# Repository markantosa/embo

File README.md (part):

# EMBO — Embolization Particle Sizing System

> SUTD 30.007 Engineering Design Innovation | Team EMBO | Week 13 of 13

EMBO is a closed-loop medical device that automates and quality-controls the preparation of gelatin foam embolic agents for interventional radiology procedures. It is the first device of its kind to measure and control particle size during embolic agent preparation in real time.

| | |
|:---:|:---:|
|  |  |
| *Fully assembled device* | *Electrical assembly* |

**CAD renders**

| Isometric | Front | Sheet-metal enclosure |
|:---:|:---:|:---:|
|  |  |  |
| *First concept render (Blender)* | *First concept render (Blender)* | *CAD (Fusion 360)* |

---

## The Problem

Embolization procedures use tiny gelatin foam particles (embolic agents) to deliberately block blood vessels — treating tumours, fibroids, and bleeding. Before every procedure, a clinician manually prepares a particle slurry by pumping two syringes back and forth until the mixture reaches a "pudding consistency." There is no measurement, no standard, and no quality check. Two clinicians doing this side by side produce slurries with completely different particle size distributions. Particle size directly affects clinical outcomes: wrong sizes can cause tissue death in unintended areas or fail to block the target vessel.

**No device currently exists to measure or control particle size during this preparation step.** Gelfoam has been used since the 1970s with the preparation method unchanged.

---

## What EMBO Does

EMBO replaces manual syringe pumping with a controlled, sensor-guided system that:

1. **Automates mixing** — two stepper motors drive syringe plungers back and forth with precise speed, stroke, and cycle control
2. **Measures particle size** using two independent sensing modalities:
   - **Ultrasound attenuation (UAS)** — a 1 MHz acoustic signal chain measures how much sound energy the slurry absorbs; larger particles attenuate more. This is the **closed-loop** measurement the mixing stop condition actually runs on.
   - **Computer vision (verification only)** — a Raspberry Pi Zero 2W + OV9281 global-shutter mono camera captures a frame on demand and runs it through a Roboflow-hosted instance-segmentation model, reporting median particle size and IQR plus a segmentation-blob-annotated photo. This is an **optional, operator-triggered check**, not a continuous control input — see "Sensing System" below for why.
3. **Stops automatically** when the target particle size is reached, using a closed-loop control scheduler on the ESP32-S3 driven by the UAS delta-voltage size equation, adjusting stroke-by-stroke based on live sensor feedback. The target is adjustable per procedure (50–1000 µm, set via the touchscreen/encoder), since the ideal size depends on which vessels are being treated.

---

## System Architecture

```
┌─────────────────────────────────────────────────────────────────┐
│                        EMBO Device                              │
│                                                                 │
│  ┌──────────────────┐          ┌──────────────────────────────┐ │
│  │ Raspberry Pi     │◄─UART──►│     ESP32-S3 MCU Board       │ │
│  │ Zero 2W          │          │                              │ │
│  │  - Roboflow      │          │  - Scheduler control loop    │ │
│  │    hosted CV     │          │    (UAS delta-V closed loop) │ │
│  │    (on-demand)   │          │  - 2× TMC2209 motor drivers  │ │
│  │  - Particle size │          │  - UAS signal chain          │ │
│  │    + annotated   │          │  - ILI9341 TFT UI (LovyanGFX)│ │
│  │    photo         │          │  - BLE debug (NimBLE)        │ │
│  │  - OV9281 CSI    │          │                              │ │
│  │    mono camera   │          │                              │ │
│  └──────────────────┘          └──────────────────────────────┘ │
│           │                             │           │            │
│           ▼                             ▼           ▼            │
│    [Camera + LED]              [Stepper motors] [UAS Transducers]│
│    [Backlight panel]           [Limit switches] [SMA connectors] │
└─────────────────────────────────────────────────────────────────┘
```

### Particle Size Model

Mixing follows first-order breakage kinetics:

```
D(N) = D_min + (D₀ − D_min) × e^(−kN)
```

Where `N` is stroke count, `k` is a shear constant (measured empirically), `D₀` is initial particle size, and `D_min` is the minimum achievable size. The mixing scheduler uses live measurements of `D(N)` (via the UAS delta-V equation) to decide when to stop.

---

## Repository Structure

```
EMBO/
├── README.md
├── .gitignore
│
├── docs/                              # Design documents and briefs
│   ├── EMBO_Project_Overview.md       # Project context — public/general audience
│   ├── EMBO_PCB_Design_Brief_v3_4.txt # Complete electrical design spec (current)
│   ├── EMBO_PCB_Design_Brief_v3_4.docx / .pdf
│   ├── EMBO_PCB_Design_Brief_v2.51.txt# Superseded — kept for reference
│   └── EMBO_Pinout_Cheatsheet.txt     # Quick GPIO and connector reference (being updated for v3.4)
│
├── hardware/
│   ├── electrical/                    # KiCad schematics + PCB layout — 2 boards:
│   │   │                              #   main board (v3.4, current) + display breakout
│   │   └── README.md
│   └── mechanical/                    # CAD files (SolidWorks / Fusion 360)
│                                      #   Final Pure Assembly.f3z is the current top-level assembly
│       └── README.md
│
├── firmware/
│   └── esp32/                         # ESP32-S3 Arduino/C++ firmware (PlatformIO)
│       ├── README.md                  # Flash guide and peripheral notes
│       └── ../FIRMWARE_TODO.md        # Build-up task list + hardware checklist
│
├── software/
│   ├── SOFTWARE_TODO.md               # Original CV pipeline build-up task list (superseded, kept for reference)
│   ├── cv_verify/                     # CURRENT — on-demand CV verification, Pi Zero 2W
│   │   ├── SESSION_HANDOFF.md         # Latest working state, Roboflow wiring, hardware notes
│   │   ├── main.py                    # Request/reply loop: waits for CAPTURE, replies SIZE + annotated IMG
│   │   ├── capture.py / preprocessing.py / link.py / config.py
│   │   └── SETUP.md                   # Pi Zero 2W flash/SSH/dev setup
│   └── cv-pipeline/                   # Legacy — original continuous-loop design, Pi 5 + YOLOv8.
│       │                              # detection.py/sizing.py now live here and are imported by
│       │                              # cv_verify/main.py (loop-agnostic), but the driving loop itself
│       │                              # moved to cv_verify/ — see cv_verify/TODO.md for why.
│       └── README.md
│
├── testing/
│   ├── PCB_Test_Firmware_v3_4/        # v3.4 bench-test firmware + Web Bluetooth sensor dashboard
│   └── CV_Verify_UART_Prototype/      # Throwaway prototype that proved out the IMG-over-UART
│                                      # protocol ahead of real detection/sizing existing — since
│                                      # merged into firmware/esp32/ directly, kept for reference
│
└── assets/                            # Images, diagrams, photos
```

Note: TFT touchscreen UI code lives in `firmware/esp32/src/ui.cpp` and is tracked in `firmware/FIRMWARE_TODO.md` — there's no separate `software/ui/` folder, since that code only runs on the ESP32, not the Pi.

---

## Hardware Overview

### Main MCU Board (ESP32-S3) — v3.4

| Subsystem | Components |
|---|---|
| Microcontroller | ESP32-S3-WROOM-1-N4 (4MB flash, no PSRAM, BLE 5.0, USB-C native programming) — corrected from N8 in v3.3, no pinout impact |
| Motor drivers | 2× MKS TMC2209 V2.0 plug-in modules in 2×8 sockets, field-replaceable; MS1/MS2 jumpers (new v3.4) make both modules interchangeable across UART addresses |
| Ultrasound signal chain | AD9833 DDS → OPA2354 Tx (G=4.9, 2.96Vpp) → transducer → OPA2354 Rx (G=100, interstage AC-coupled) → BAT54 envelope → GPIO1 ADC |
| Turbidity sensing | APDS9960 (I2C 0x39, ALS transmission) + MAX30102 (I2C 0x57, backscatter), shared I2C bus |
| Force sensing | 2× load cell + HX711 amplifier, socketed, shared-clock bit-bang driver — hardware fallback for StallGuard SG_RESULT |
| Display | ILI9341 SPI TFT + XPT2046 resistive touch via 20-pin IDC ribbon to breakout board |
| Power | 24V PSU → F1 (off-board T5A fuse) → F2 (on-board 8A backstop, new v3.4) → AO4407A reverse polarity protection → LM2596 buck (5V) → AMS1117 LDO (3.3V) |
| Comms | UART2 to Raspberry Pi (921600 baud, GPIO47/48); BLE UART debug stream (NimBLE) |

v3.4 is a hardware-hardening pass: 12× 220Ω GPIO protection resistors on every ESP32-to-TMC2209 control line (added after a hot-swap/spark incident on the fabricated v2.51 board), the PDN_UART pin correction (module pin 5, not pin 4), and a full reference-designator naming pass. See [`hardware/electrical/README.md`](hardware/electrical/README.md) for the complete changelog.

| | | |
|:---:|:---:|:---:|
|  |  |  |
| *3D render, front* | *3D render, back* | *KiCad trace routing — L1 + L4 (L2 GND, L3 3V3 hidden for clarity)* |

| | |
|:---:|:---:|
|  |  |
| *Fabricated board — bring-up* | *Fabricated board — wired up* |

### GPIO Assignments (key signals)

| GPIO | Signal | Notes |
|---|---|---|
| 1 | UAS_ADC | ADC1_CH0 — envelope detector output |
| 3/43 | I2C_SDA/SCL | Shared bus, APDS9960 (0x39) + MAX30102 (0x57), 400kHz |
| 4/44 | TMC_UART TX/RX | Half-duplex, shared PDN bus, via 1kΩ + 220Ω GPIO protection per module |
| 5/8 | STEP_M1/M2 | Hardware timer — step pulse generation, 220Ω GPIO protection |
| 6/9 | DIR_M1/M2 | Motor direction, 220Ω GPIO protection |
| 7/10 | EN_M1/M2 | Motor enable (active LOW, 10kΩ pull-up at IC), 220Ω GPIO protection |
| 14/15 | LIMIT_M1/M2 | Limit switch inputs (internal pull-up) |
| 19/20 | USB D−/D+ | Fixed USB PHY — no UART bridge chip needed |
| 21/37/42 | HX711_2_DT / SCK (shared) / HX711_1_DT | 2× load cell amplifiers, shared clock |
| 35/36 | SPI MOSI/CLK | Shared: AD9833 (Mode 2) + ILI9341 + XPT2046 (Mode 0) |
| 47/48 | RPi TX/RX | UART2 to Raspberry Pi, 921600 baud |

### Display Breakout Board — 2-layer PCB

ILI9341 TFT + XPT2046 touch controller on a separate board, connected to the main MCU board via a 20-pin IDC ribbon.

| | |
|:---:|:---:|
|  |  |
| *PCB layout* | *3D render* |

### Sensing System

**Ultrasound Attenuation Sensing (UAS):**
- AD9833 generates 1 MHz sine wave → OPA2354 Tx amp (G=4.9, 2.96Vpp output) → J1 SMA → transducer
- Received signal → J2 SMA → BAV99 protection → OPA2354 two-stage Rx (10× + 10× = 100× total) → BAT54 envelope detector → GPIO1
- Firmware reads attenuation ratio vs saline baseline to track particle size change

**Computer Vision (verification, not closed-loop control):**
- Raspberry Pi Zero 2W + OV9281-110 global-shutter mono CSI camera — no dye/contrast agent added to the slurry (real medical-device material), so contrast comes entirely from dark-field/oblique illumination and software-side local-contrast enhancement
- Operator-triggered only: the ESP32 sends `CAPTURE` over UART, the Pi captures + median-stacks frames (noise reduction), runs instance segmentation via a Roboflow-hosted model (RF-DETR, trained on ~100 collected samples), and replies with `SIZE <median_um> <iqr_um>` plus a downscaled photo with segmentation blob outlines baked in — both rendered on the touchscreen's Camera Verify screen side by side, with an IN SPEC/OUT OF SPEC check
- **Not a fusion input** — unlike UAS, a CV result never drives the mixing stop condition; worst case for a failed/slow capture is a timeout notice, not a stalled run. See `software/cv_verify/TODO.md` for the full reasoning
- Diffused LED panel (5V, J8) backlit behind syringe for particle contrast

**Turbidity Sensing (added v3.2, hardened v3.4):**
- APDS9960 (I2C 0x39) reads ALS clear-channel transmission through the syringe; external LED hardwired on
- MAX30102 (I2C 0x57) reads backscatter using its own onboard 660/880nm LEDs
- Shared I2C bus (GPIO3/GPIO43, 400kHz); independent of the UAS acoustic path — a second, optical estimate of slurry turbidity
- Live readings viewable on the BLE **Telemetry Dashboard** (`firmware/esp32/web/`) as Optical Sensor 1/2, alongside every other sensor — see "Getting Started" below
- Like CV, not yet part of the mixing stop condition — the fusion calibration table (`calibration.cpp`) is still unfilled placeholder data for every channel, so only UAS drives the closed loop today

**Force Sensing (added v3.2):**
- 2× load cell + HX711 24-bit amplifier at the syringe plunger contact point
- Shared-clock, per-channel data line — custom bit-bang driver (standard HX711 libraries assume one dedicated clock per chip)
- Hardware fallback for TMC2209 StallGuard SG_RESULT if the UART-based reading proves unreliable

---

## Firmware Status

| Module | File | Status |
|---|---|---|
| TMC2209 UART, SpreadCycle, StallGuard | `src/motors.cpp` | ✅ Done |
| LEDC step generation, limit switch ISRs | `src/motors.cpp` | ✅ Done |
| Homing routine + stroke counter | `src/motors.cpp` | ✅ Done |
| AD9833 1MHz DDS, UAS ADC calibration | `src/uas.cpp` | ✅ Done |
| NimBLE wireless debug UART + binary telemetry service | `src/ble_debug.cpp`, `src/ble_binary_telemetry.cpp` | ✅ Done |
| RPi UART: SIZE reply parsing + on-demand IMG (annotated photo) receive | `src/rpi_uart.cpp` | ✅ Done |
| Mixing scheduler: adjustable setpoint (50–1000µm), closed-loop UAS delta-V stop condition | `src/scheduler.cpp` | ✅ Done — replaces the old PID design |
| TFT UI: encoder-driven menus, live verify screen (photo + PSD/IQR), start/stop-estop | `src/ui.cpp`, `src/ui/screens/` | ⚠️ Touch input still stub (encoder-only works) |
| Turbidity sensors (APDS9960 + MAX30102) | `src/turbidity.cpp` | ✅ Done — feeds the BLE Telemetry Dashboard; not yet a fusion input (calibration table unfilled) |

See [`firmware/FIRMWARE_TODO.md`](firmware/FIRMWARE_TODO.md) for the full task list and hardware bring-up checklist, and [`firmware/esp32/README.md`](firmware/esp32/README.md#operational-workflow) for the doctor-facing operational workflow (boot → home → set target → run → stop/e-stop).

---

## Software Stack

| Layer | Platform | Language | Key Libraries |
|---|---|---|---|
| Computer vision (on-demand verification) | Raspberry Pi Zero 2W | Python 3 | picamera2, Pillow, NumPy, `requests` (Roboflow hosted inference — see `software/cv_verify/detection.py`) |
| Firmware / mixing scheduler | ESP32-S3 | C++ (Arduino) | TMCStepper, NimBLE, LovyanGFX, AD9833 |
| Touchscreen UI | ESP32-S3 | C++ | LovyanGFX |
| BLE debug + telemetry | ESP32-S3 | C++ | NimBLE |

**Critical firmware notes:**
- SPI2 is shared between AD9833 (Mode 2, ~10MHz), ILI9341 (Mode 0, 20MHz max via ribbon), and XPT2046 (Mode 0, 2MHz). Each library switches mode per transaction via `SPI.beginTransaction()`.
- TMC2209 uses a half-duplex UART bus (GPIO4 TX / GPIO44 RX as of v3.4). Raspberry Pi uses UART2 (GPIO47/48). These are separate peripherals — do not reassign.
- ADC1 (GPIO1) is safe while BLE is active. ADC2 cannot be used for analog during BLE — no ADC2 pins are used for analog in this design.
- SpreadCycle must be written via UART to both TMC2209 modules at every boot (no SPREAD pin on the MKS V2.0 modules). BLE log confirms success.
- HX711 reads are pinned to core 1 and short-critical-sectioned — PD_SCK must never sit HIGH past ~60µs or the chip powers itself down mid-read.

---

## Team Structure

| Sub-team | Responsibilities | Members |
|---|---|---|
| **Mechanical** | Frame, syringe holders, motor mounts, 3D printed enclosure (FDM + SLA resin), DOE (Design of Experiments) | Alvin, Victoria, Tian Wen |
| **Electrical & Software** | KiCad schematics + PCB layout (main board + display breakout), component sourcing, board bring-up/testing, ESP32-S3 firmware (mixing scheduler, motor control, UAS), RPi CV verification pipeline (Roboflow), TFT UI | Vincent, Ren Jie, Audrey, Aditi |

---

## Project Timeline

| Milestone | Week | Status |
|---|---|---|
| System Requirements Review | 5 | ✅ Complete |
| Recess week — build sprint | 7 | ✅ Complete |
| PCB schematic freeze | End of 7 | ✅ Complete |
| System Design Review | 9 | ✅ Complete |
| Final Exhibition | 13 | ✅ Current |

---

## Getting Started

### Firmware (ESP32-S3)

Requires VS Code + PlatformIO extension. See [`firmware/esp32/README.md`](firmware/esp32/README.md) for the full flash guide.

```bash
# Quick start
cd firmware/esp32
pio run --target upload   # build and flash
pio device monitor        # serial monitor at 115200
```

Hold `BOOT` + press `RESET` for manual bootloader entry if auto-reset fails.

### Computer Vision Pipeline (Raspberry Pi Zero 2W)

```bash
cd software/cv_verify
python3 -m venv .venv --system-site-packages   # --system-site-packages: sees apt-installed picamera2
source .venv/bin/activate
pip install -r ../requirements.txt
export ROBOFLOW_API_KEY=<your key>             # not stored in any committed file
python3 main.py
```

See [`software/cv_verify/SETUP.md`](software/cv_verify/SETUP.md) for full Pi Zero 2W bring-up (camera/UART dtoverlays, etc.) and [`software/cv_verify/SESSION_HANDOFF.md`](software/cv_verify/SESSION_HANDOFF.md) for current working state and known issues.

### Electrical

PCB files live in `hardware/electrical/` — two boards: the main board (`embo main MCU PCB v3_4/`, current revision) and the display breakout. Open with KiCad 10. The full design spec including component values, GPIO assignments, layout rules, BOM, and the pre-submission checklist is in [`docs/EMBO_PCB_Design_Brief_v3_4.txt`](docs/EMBO_PCB_Design_Brief_v3_4.txt).

### Telemetry Dashboard (real firmware)

`firmware/esp32/web/index_logging to record UAS csv data.html` is a Web Bluetooth dashboard for the actual production firmware (not the bench-test project below) — live UAS envelope, both load cells, and both optical/turbidity sensors (labeled Optical Sensor 1/2), plus motor jog/home controls and the automated UAS frequency sweep. Requires BLE to be enabled on-device first (**Settings → Developer mode → UAS debug mode**), and must be served over http(s) — Web Bluetooth silently fails under a `file://` URL:

```bash
cd firmware/esp32/web
python3 -m http.server 8000
# open http://localhost:8000/index_logging%20to%20record%20UAS%20csv%20data.html
```

### PCB Bench-Test Firmware + Dashboard

`testing/PCB_Test_Firmware_v3_4/` is a separate, standalone PlatformIO project for bringing up an assembled v3.4 board pre-final-firmware: reads every sensor (UAS envelope, both load cells, both turbidity channels, both StallGuard results, limit switches), drives the two steppers, and streams it all over BLE to its own Web Bluetooth dashboard (`web/index.html`) with live strip-charts alongside the raw numbers.

---

## Key References

- Yamagami et al., *The Size of Gelatin Sponge Particles*, CardioVascular and Interventional Radiology, 2006
- Yamamoto et al., CVIR 1997 — liver necrosis vs particle size
- PMC8670118 — hemorrhoidal embolization outcomes
- TMC2209 Datasheet — StallGuard4, SpreadCycle, UART addressing
- AD9833 Datasheet — DDS signal generator, SPI Mode 2
- OPA2354 Datasheet — 250MHz GBW dual op-amp, single-supply operation
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
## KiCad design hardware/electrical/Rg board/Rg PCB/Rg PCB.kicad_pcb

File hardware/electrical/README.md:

# Electrical — Custom MCU Board

KiCad schematic and PCB layout for the EMBO ESP32-S3 control board.

Current fabricated/in-progress revision: **v3.4** (`hardware/electrical/embo main MCU PCB v3_4/`).
The prior `embo main MCU PCB v2_5/` folder is kept for reference only — see
below for what changed between them.

## Design spec

Full design specification, component values, GPIO assignments, layout rules, BOM, and pre-submission checklist:
[`/docs/EMBO_PCB_Design_Brief_v3_4.txt`](../../docs/EMBO_PCB_Design_Brief_v3_4.txt)

Quick GPIO and connector reference:
[`/docs/EMBO_Pinout_Cheatsheet.txt`](../../docs/EMBO_Pinout_Cheatsheet.txt)
(being updated for v3.4 — treat the design brief above as authoritative in the meantime)

## Quick reference

- **MCU:** ESP32-S3-WROOM-1-N4 (4MB flash, no PSRAM, PCB antenna) — corrected from N8 in v3.3; no pinout impact, flash capacity only affects OTA partitioning
- **Motor drivers:** 2× MKS TMC2209 V2.0 plug-in modules in 2×8 sockets — field-replaceable, MS1/MS2 jumpers make both modules interchangeable across UART addresses 0–3 (new v3.4)
- **Turbidity sensing:** APDS9960 (I2C 0x39, ALS transmission) + MAX30102 (I2C 0x57, backscatter), shared I2C bus
- **Force sensing:** 2× load cell + HX711 amplifier, socketed, shared-clock — hardware fallback for StallGuard SG_RESULT
- **Signal generator:** AD9833 plug-in breakout module (VCC/DGND/SDATA/SCLK/FSYNC/AGND/OUT)
- **Fuse:** 5×20mm slow-blow glass, 5A 250V (T5A), off-board PRIMARY, inline before J14 — **new v3.4:** on-board 8A SMD backstop fuse F2, deliberately rated above F1 so it never coordinates against it
- **Fabrication target:** JLCPCB, 2-layer FR4 ENIG, hot-plate reflow (AD9833/OPA2354 only — TMC2209/HX711 modules are hand-socketed)
- **Schematic tool:** KiCad 10
- **Power rails:** 24V PSU → F1 (off-board) → F2 (on-board backstop) → AO4407A reverse polarity protection → LM2596 buck (5V) → AMS1117 LDO (3.3V)

## v3.4 summary of changes (from v3.3)

This revision is a hardware-hardening and naming-discipline pass, prompted by (a) a live TMC2209 hot-swap incident on the fabricated v2.51 board that sparked and left the ESP32 module overheating on every subsequent power-up, and (b) every passive finally getting an individual reference designator (full lookup table in the design brief §12.3), closing a BOM gap that had gone uncounted.

- **Full reference-designator naming pass** — every resistor, capacitor, diode, the inductor, and both LEDs now has an explicit, unique ref designator
- **On-board backstop fuse F2** — 8A SMD slow-blow (Littelfuse Nano2 452-series), in series after Q1, sized *above* the primary inline T5A so it never coordinates against it; only catches an empty/bypassed/mis-fitted F1 holder
- **TMC2209 UART pin correction** — physical inspection of the MKS V2.0 module's own silkscreen found pin 5 (not pin 4) is the direct PDN_UART node — the opposite of every version through v3.3, which followed generic third-party SilentStepStick documentation instead of this specific module's markings. Jumper default flipped on both U5 and U6.
- **MS1/MS2 address jumpers** — both modules gain 1×3+shunt jumpers on MS1 and MS2 (4 headers total), making U5/U6 fully interchangeable spares instead of hardwired at fixed addresses
- **GPIO short-fault protection** — a 220Ω series resistor on every ESP32-to-TMC2209 control line (STEP, DIR, EN, PDN_UART, MS1, MS2 × 2 modules = 12 resistors), added directly in response to the hot-swap/spark incident on the v2.51 board
- **UAS Tx/Rx hardening** — Tx gain resistor (RfO1_1, 390Ω) changes SMD → THT for field gain adjustment (fixed value, deliberately not a trimpot); Rx chain gains an interstage AC-coupling network ahead of the ×10.1 second stage
- **Component package/procurement changes** — TMC2209 VM bulk caps SMD radial (8mm, beside not under each socket); J14 screw terminal 3.5mm → 5.0mm pitch; boot/reset buttons SMD 6×6 → THT 6mm tactile
- **24V power LED wired** — taps the *protected* rail (Q1 Source), not raw input, so it only lights when Q1 is actually passing current correctly

See the design brief's revision history (§0) for the full v2.0 → v3.4 changelog, and §13 for the pre-submission checklist and open items carried forward from the fabricated v2.51 board (LM2596 buck fault workaround, TMC2209 hot-swap short diagnosis).

## Critical layout rules

- ESP32-S3 antenna keepout: 15mm clear on **all layers** including ground plane
- AMS1117 SOT-223 tab must connect to ≥100mm² copper pour with ≥4 thermal vias
- LM2596 catch diode (SS34A) within 5mm of SW pin, same layer, minimal loop area
- UAS analog traces on top layer only, no vias, routed over uninterrupted ground pour
- C_adc (100nF) within 2mm of GPIO1; C_envRC1 (10nF) distinct component from C_adc
- SK1/SK2: PDN routes to the jumper-selected pin (pin 5 direct = default, pin 4 via on-module R8 = fallback) through its 220Ω GPIO protection resistor — never shunt both jumper positions at once
- All 12 GPIO protection resistors (STEP/DIR/EN/PDN/MS1/MS2 × 2 modules) placed in series at the socket boundary, not upstream at the MCU
- TMC2209 VM bulk caps (100µF SMD radial, 8mm height) placed *beside* each socket, not underneath — clearance for the socket + module stack
- Q1 (AO4407A): Drain → input (J14 side), Source → load (24V rail) — reversed from v3.1, bench-verify ~0mA reverse-polarity draw before trusting the board
- Power off and allow VM bulk caps to fully discharge before inserting/removing any TMC2209 module — procedural rule added after the v2.51 hot-swap/spark incident

## TMC2209 module addressing

MS1/MS2 are field-jumpered as of v3.4 (previously hardwired), making U5 and U6 fully interchangeable spares:

| Driver | Module | MS1 jumper | MS2 jumper | UART address |
|---|---|---|---|---|
| Motor 1 | U5 (SK1) | GND (no shunt) | GND (no shunt) | 0 |
| Motor 2 | U6 (SK2) | 3.3V via 10kΩ (JMP_MS1_T2) | GND (no shunt) | 1 |

Shared half-duplex PDN_UART bus: GPIO4 (TX) / GPIO44 (RX) via R_UART (1kΩ) + R_PDN_UP (10kΩ pull-up to 3.3V), through each module's 220Ω GPIO protection resistor to its jumper-selected pin (pin 5 direct by default, §7.3 of the design brief).

## Screenshots

### Main MCU board — v3.4 (current)

| | | |
|:---:|:---:|:---:|
|  |  |  |
| *Assembled board, front* | *Assembled board, back* | *KiCad PCB editor view* |

### Main MCU board — earlier render (v2.5)

| | |
|:---:|:---:|
|  |  |
| *PCB layout* | *3D render* |

### Display breakout board

Pinout and IDC ribbon interface unchanged since v2.4 — carried forward as-is into v3.4.

| | |
|:---:|:---:|
|  |  |
| *PCB layout* | *3D render* |

## Firmware bring-up dependency

SpreadCycle cannot be set by hardware (no SPREAD pin on the MKS V2.0 modules). Firmware **must** write `GCONF.en_spreadcycle=1` to both drivers at every boot and read back to confirm before trusting StallGuard data. See [`firmware/FIRMWARE_TODO.md`](../../firmware/FIRMWARE_TODO.md) for the full hardware bring-up checklist, and [`testing/PCB_Test_Firmware_v3_4/`](../../testing/PCB_Test_Firmware_v3_4/) for the v3.4 bench-test firmware and Web Bluetooth sensor dashboard.

## Open items (carried forward from the fabricated v2.51 board)

- **LM2596 (U2) buck fault** — external buck module workaround in place; U2 itself never bench-verified standalone
- **TMC2209 hot-swap short** — the ESP32 module is suspected damaged from the v2.51 hot-swap/spark incident; diagnosis in progress (unpowered 3V3-to-GND resistance check, ESP32 isolation)
- **AD9833 real output amplitude** — never measured on a scope; every UAS gain figure in the design brief rests on the datasheet-typical ~0.6Vpp, not a confirmed measurement

## Schematic status

v3.4 is a full rebuild in 8 wiring blocks (per team request) — see the design brief for the pre-submission checklist (§13) before sending to fab.

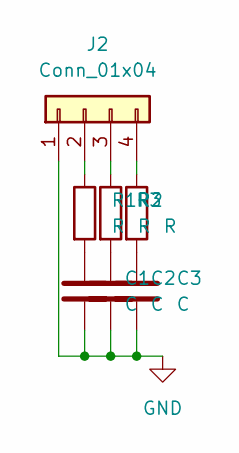
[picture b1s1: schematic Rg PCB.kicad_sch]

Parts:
C1, C2, C3: C; C_Disc_D5.0mm_W2.5mm_P5.00mm
J2: Conn_01x04; PinHeader_1x04_P2.54mm_Vertical
R1, R2, R3: R; R_Axial_DIN0207_L6.3mm_D2.5mm_P7.62mm_Horizontal

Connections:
GND: C1.2, C2.2, C3.2, J2.1
unnamed: C1.1, R1.2
unnamed: C2.1, R2.2
unnamed: C3.1, R3.2
unnamed: J2.2, R1.1
unnamed: J2.3, R2.1
unnamed: J2.4, R3.1

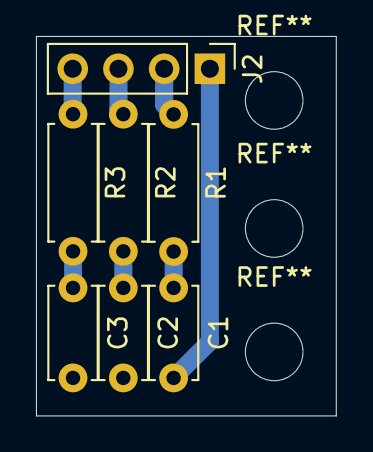
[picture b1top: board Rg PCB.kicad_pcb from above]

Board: 2 copper layers, 16.7 x 21.1 mm, 7 parts (0 on the bottom side), 7 nets.

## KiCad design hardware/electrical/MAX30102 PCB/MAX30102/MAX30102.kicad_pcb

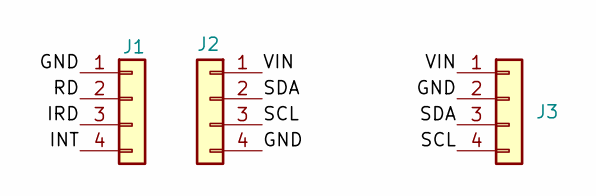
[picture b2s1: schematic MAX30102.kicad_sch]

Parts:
J1, J2: Conn_01x04; PinSocket_1x04_P2.54mm_Vertical
J3: Conn_01x04; JST_XH_B4B-XH-A_1x04_P2.50mm_Vertical

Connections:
/GND: J1.1, J2.4, J3.2
/INT: J1.4
/IRD: J1.3
/RD: J1.2
/SCL: J2.3, J3.4
/SDA: J2.2, J3.3
/VIN: J2.1, J3.1

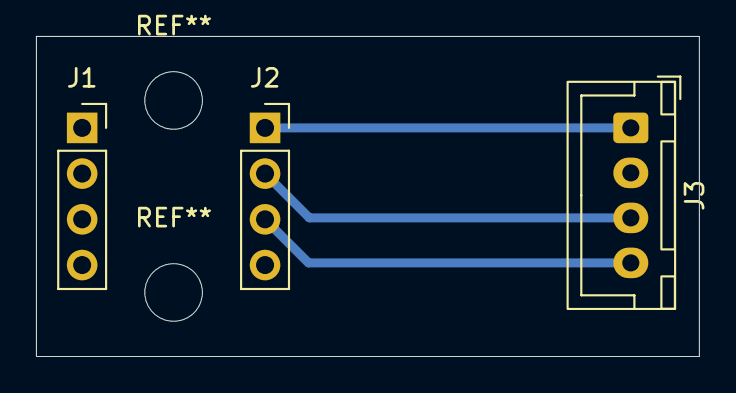
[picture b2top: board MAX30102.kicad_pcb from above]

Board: 2 copper layers, 36.8 x 17.8 mm, 3 parts (0 on the bottom side), 4 nets.

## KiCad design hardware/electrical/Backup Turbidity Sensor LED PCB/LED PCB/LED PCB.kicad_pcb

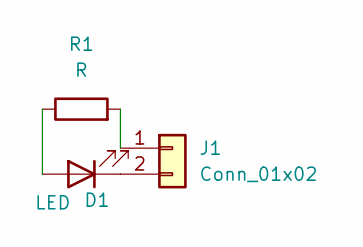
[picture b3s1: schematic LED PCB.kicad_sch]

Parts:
D1: LED; LED_D5.0mm
J1: Conn_01x02; JST_XH_B2B-XH-A_1x02_P2.50mm_Vertical
R1: R; R_Axial_DIN0207_L6.3mm_D2.5mm_P10.16mm_Horizontal

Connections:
unnamed: D1.2 (A), R1.1
unnamed: D1.1 (K), J1.2
unnamed: J1.1, R1.2

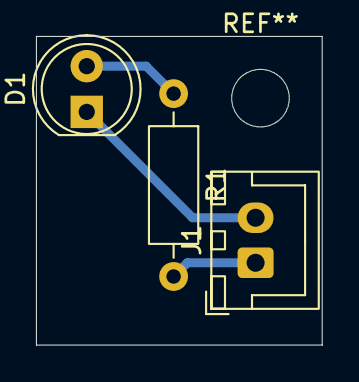
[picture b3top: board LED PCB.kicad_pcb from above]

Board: 2 copper layers, 15.9 x 17.1 mm, 3 parts (0 on the bottom side), 3 nets.

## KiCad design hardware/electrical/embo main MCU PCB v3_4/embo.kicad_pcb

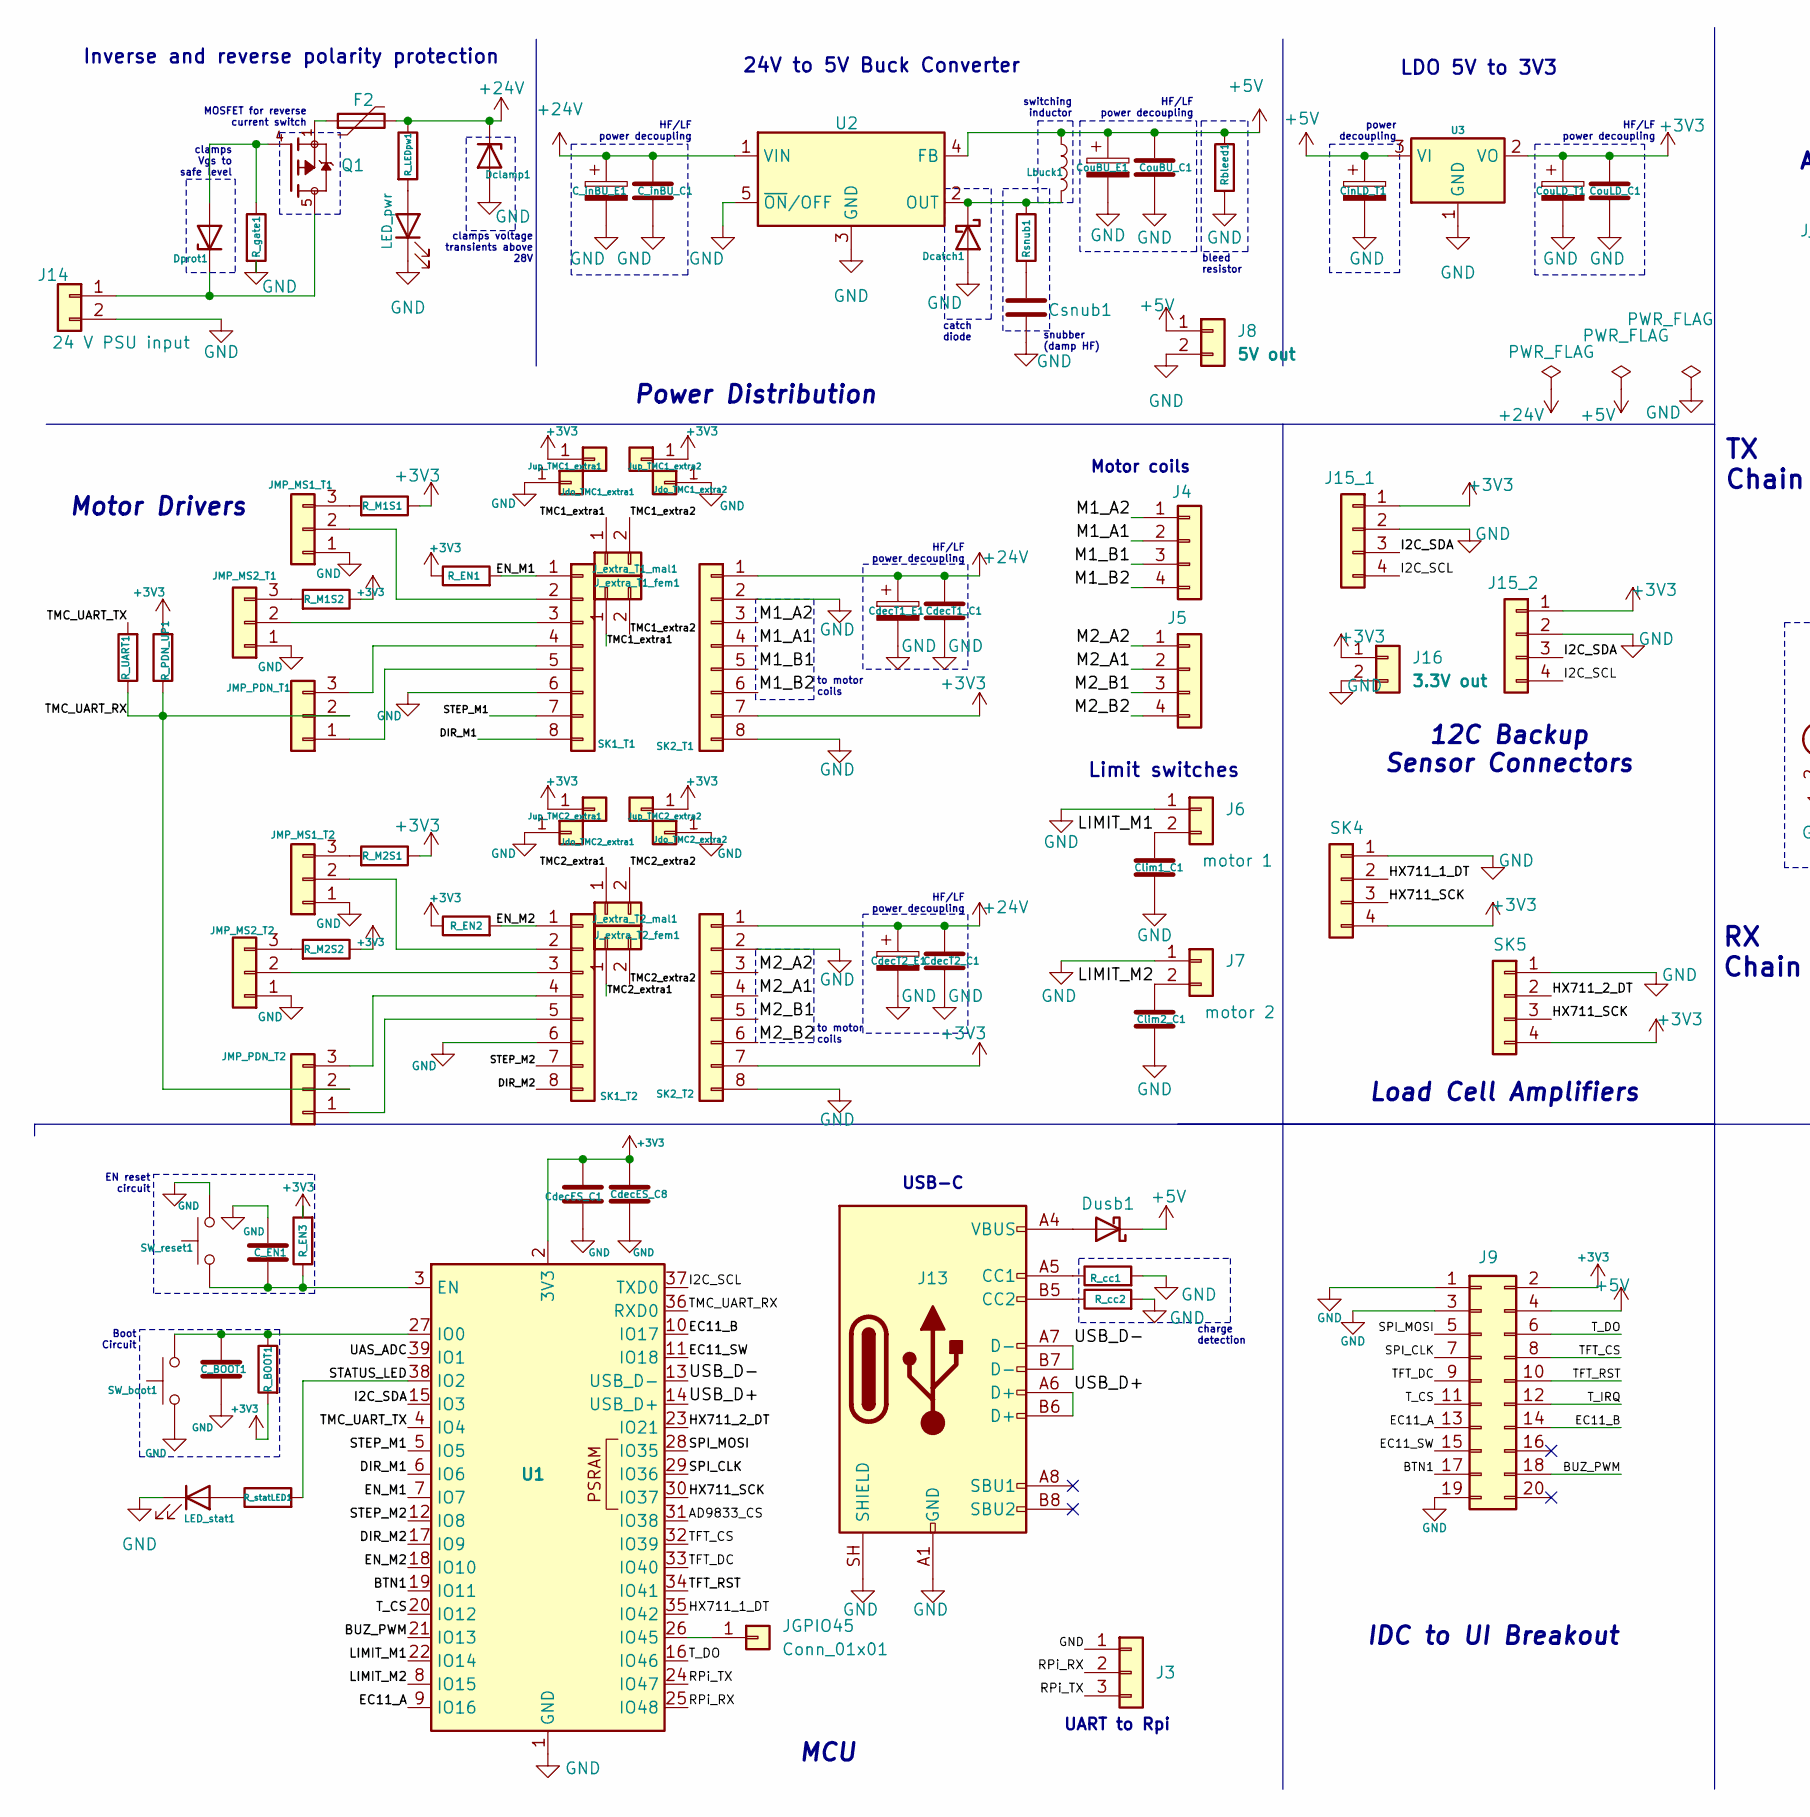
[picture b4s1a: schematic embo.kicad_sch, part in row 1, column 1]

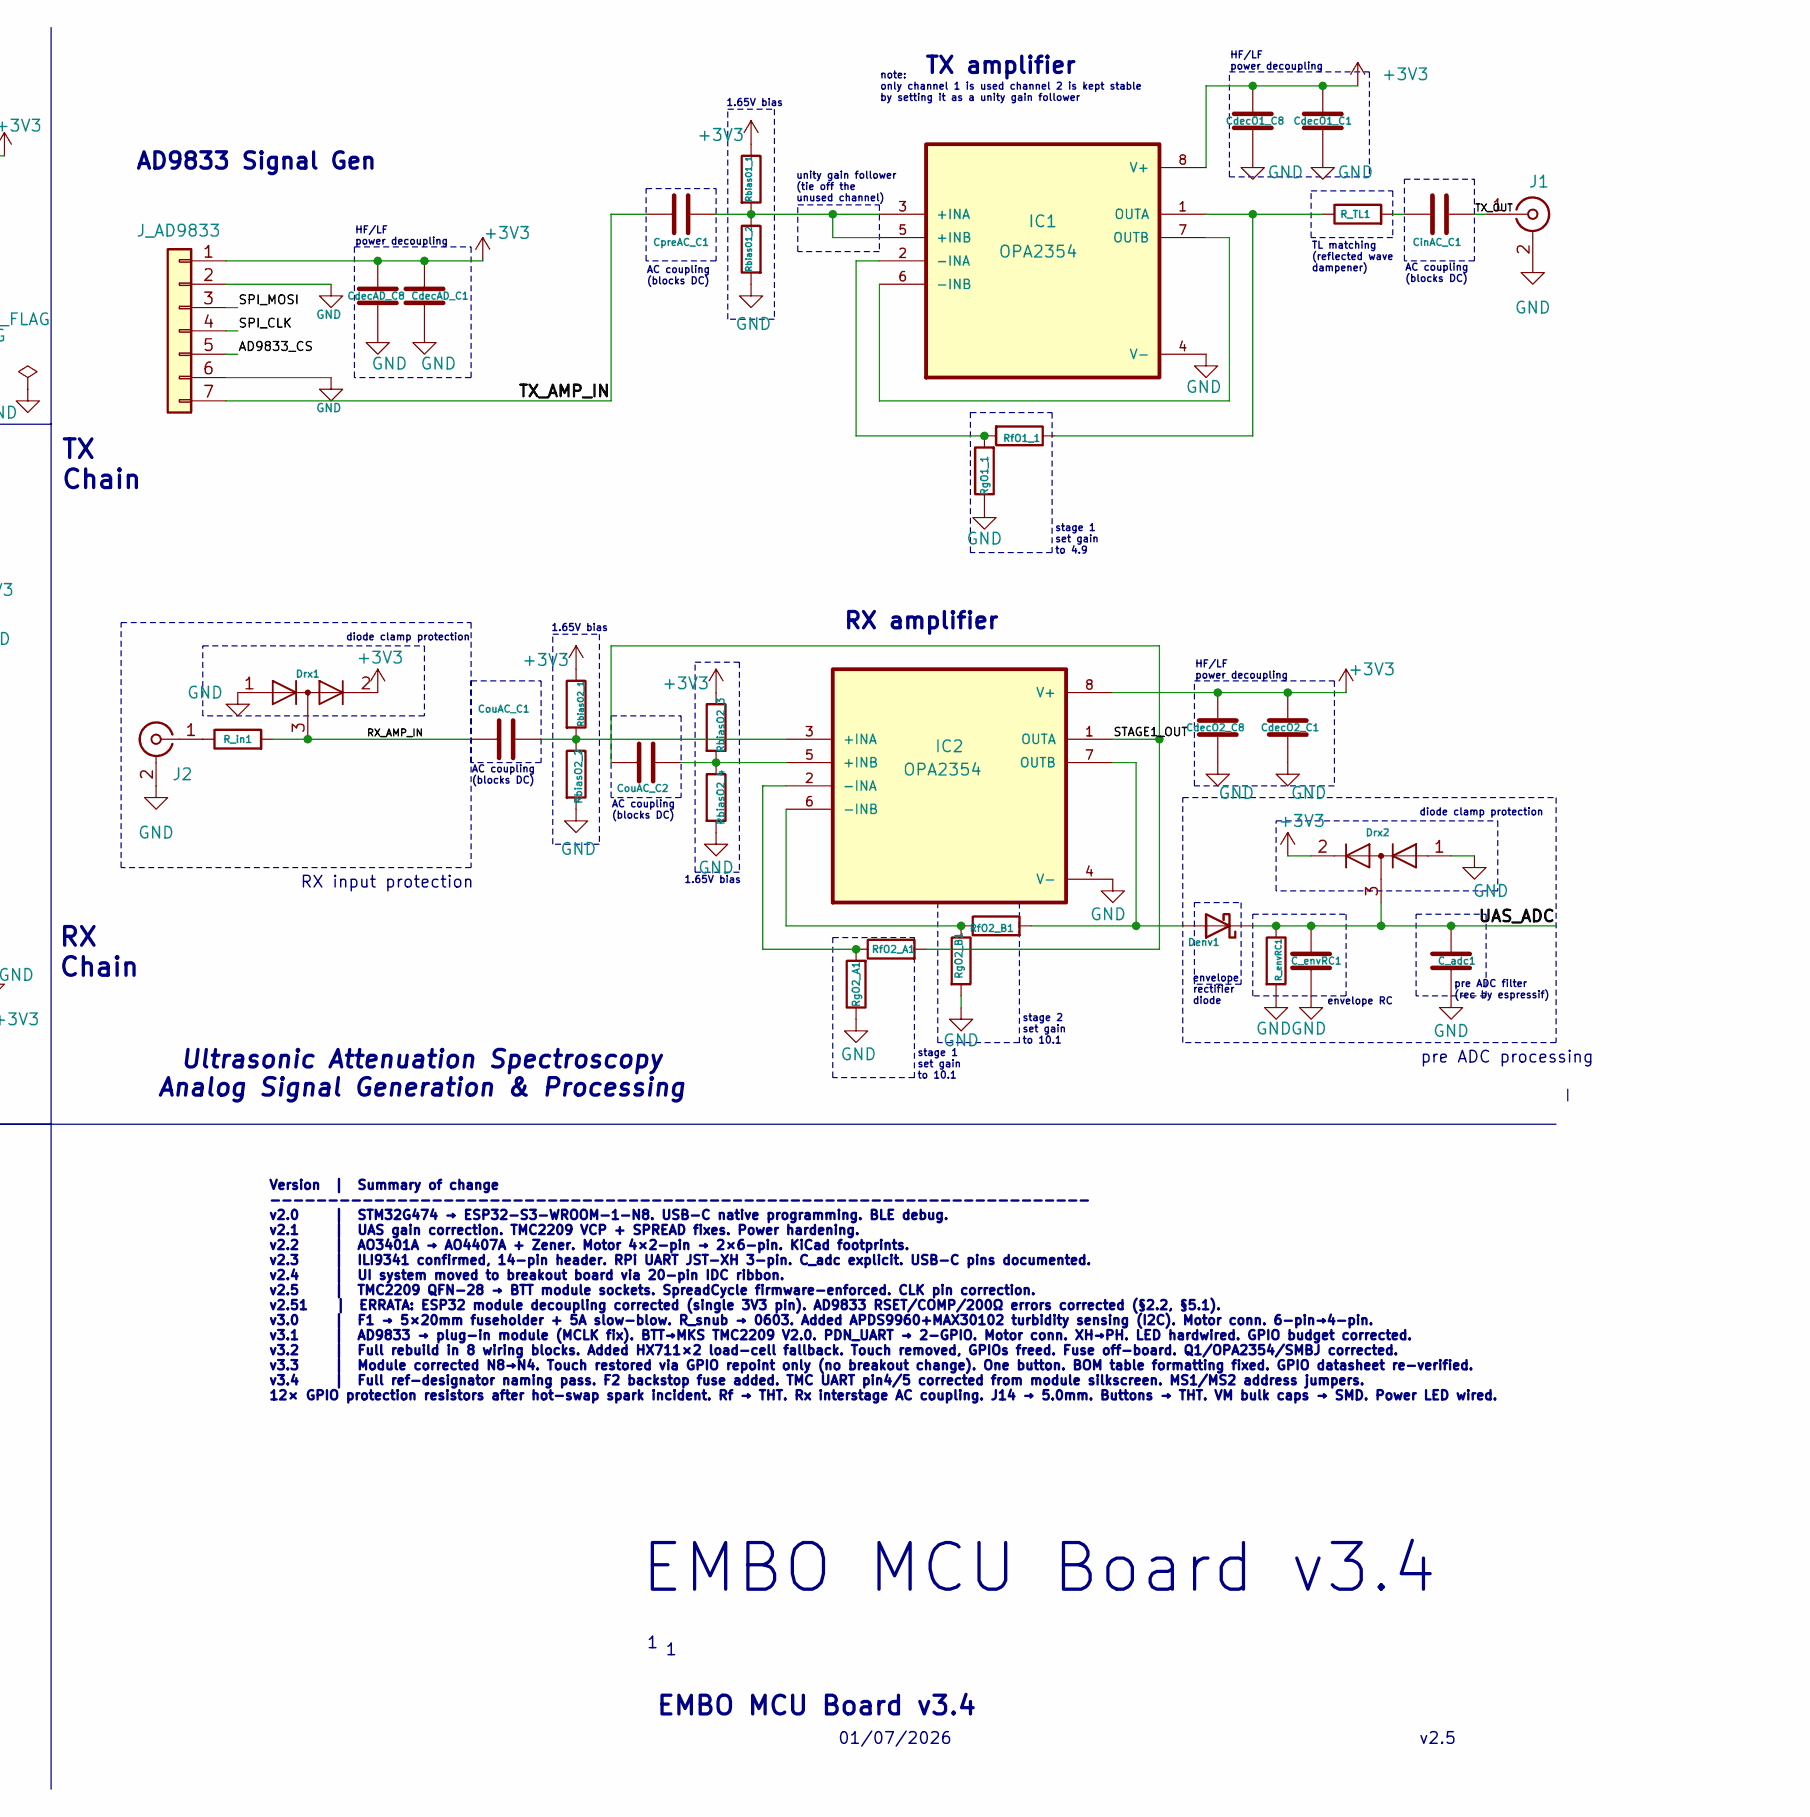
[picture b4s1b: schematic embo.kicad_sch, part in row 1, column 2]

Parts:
C_BOOT1: 100nF X7R; C_0402_1005Metric_Pad0.74x0.62mm_HandSolder
C_EN1: 1µF X7R; C_0402_1005Metric_Pad0.74x0.62mm_HandSolder
C_adc1: 100nF X7R; C_0402_1005Metric_Pad0.74x0.62mm_HandSolder
C_envRC1: 10nF X7R; C_0402_1005Metric
C_inBU_C1: 100nF X7R; C_0402_1005Metric_Pad0.74x0.62mm_HandSolder
C_inBU_E1: 100 µF 50 V radial; C_Radial_D8.0mm_H11.5mm_P3.50mm
CdecAD_C1: 100nF X7R; C_0402_1005Metric_Pad0.74x0.62mm_HandSolder
CdecAD_C8: 10µF X5R 0805; C_0805_2012Metric
CdecES_C1: 100nF X7R; C_0402_1005Metric_Pad0.74x0.62mm_HandSolder
CdecES_C8: 10µF X5R 0805; C_0805_2012Metric
CdecO1_C1, CdecO2_C1: 100nF X7R; C_0402_1005Metric_Pad0.74x0.62mm_HandSolder
CdecO1_C8, CdecO2_C8: 10µF X5R 0805; C_0805_2012Metric
CdecT1_C1, CdecT2_C1: 100nF X7R; C_0402_1005Metric_Pad0.74x0.62mm_HandSolder
CdecT1_E1, CdecT2_E1: 100µF 35V electrolytic radial; CHEMI-HA0
CinAC_C1: 100nF X7R; C_0402_1005Metric_Pad0.74x0.62mm_HandSolder
CinLD_T1: 10µF 10V tantalum Case A; CP_EIA-3216-18_Kemet-A_HandSolder
Clim1_C1, Clim2_C1: 100nF X7R; C_0402_1005Metric_Pad0.74x0.62mm_HandSolder
CouAC_C1, CouAC_C2: 100nF X7R; C_0402_1005Metric_Pad0.74x0.62mm_HandSolder
CouBU_C1: 100nF X7R; C_0402_1005Metric_Pad0.74x0.62mm_HandSolder
CouBU_E1: 220µF 10V low-ESR electrolytic radial; C_Radial_D8.0mm_H11.5mm_P3.50mm
CouLD_C1: 100nF X7R; C_0402_1005Metric_Pad0.74x0.62mm_HandSolder
CouLD_T1: 10µF 10V tantalum Case A; CP_EIA-3216-18_Kemet-A_HandSolder
CpreAC_C1: 100nF X7R; C_0402_1005Metric_Pad0.74x0.62mm_HandSolder
Csnub1: 1nF X7R; C_0402_1005Metric_Pad0.74x0.62mm_HandSolder
Dcatch1: SS34A; D_SMA
Dclamp1: SMBJ28A; D_SMA
Denv1: BAT54; D_SOD-123
Dprot1: BZX84C15, 15 V Zener, SOT-23; SOT-23
Drx1, Drx2: BAV99; SOT-23
Dusb1: 1N5819; D_SOD-123
F2: 5A littlefuse; Fuse_2512_6332Metric
IC1, IC2: OPA2354; SOIC-8_3.9x4.9mm_P1.27mm; DigiKey_Part_Number 296-25648-1-ND
J1, J2: Conn_Coaxial; SMA_Molex_73251-1153_EdgeMount_Horizontal
J3: Conn_01x03; JST_XH_B3B-XH-A_1x03_P2.50mm_Vertical
J4, J5, J15_1, J15_2: Conn_01x04; JST_XH_B4B-XH-A_1x04_P2.50mm_Vertical
J6: motor 1; JST_XH_B2B-XH-A_1x02_P2.50mm_Vertical
J7: motor 2; JST_XH_B2B-XH-A_1x02_P2.50mm_Vertical
J8: 5V out; JST_XH_B2B-XH-A_1x02_P2.50mm_Vertical
J9: Conn_02x10_Odd_Even; IDC-Header_2x10_P2.54mm_Vertical
J13: USB_C_Receptacle_USB2.0_16P; USB_C_Receptacle_HRO_TYPE-C-31-M-12
J14: 24 V PSU input; TerminalBlock_Phoenix_MKDS-1,5-2-5.08_1x02_P5.08mm_Horizont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
J16: 3.3V out; JST_XH_B2B-XH-A_1x02_P2.50mm_Vertical
JGPIO45: Conn_01x01; PinHeader_1x01_P2.54mm_Vertical
JMP_MS1_T1, JMP_MS1_T2, JMP_MS2_T1, JMP_MS2_T2: Conn_01x03; PinHeader_1x03_P2.54mm_Vertical
JMP_PDN_T1, JMP_PDN_T2: Conn_01x03; PinHeader_1x03_P2.54mm_Vertical
J_AD9833: Conn_01x07; PinSocket_1x07_P2.54mm_Vertical
J_extra_T1_fem1, J_extra_T2_fem1: Conn_01x02; PinSocket_1x02_P2.54mm_Vertical
J_extra_T1_mal1, J_extra_T2_mal1: Conn_01x02; PinHeader_1x02_P2.54mm_Vertical
Jdo_TMC1_extra1, Jdo_TMC1_extra2, Jdo_TMC2_extra1, Jdo_TMC2_extra2: Conn_01x01; PinHeader_1x01_P2.54mm_Vertical
Jup_TMC1_extra1, Jup_TMC1_extra2, Jup_TMC2_extra1, Jup_TMC2_extra2: Conn_01x01; PinHeader_1x01_P2.54mm_Vertical
LED_pwr1: LED_pwr; LED_0805_2012Metric
LED_stat1: green LED; LED_0805_2012Metric
Lbuck1: 100µH; L_Bourns_SRR1260
Q1: AO4407A; SOIC-8_3.9x4.9mm_P1.27mm; PARTREV I
R_BOOT1: 10kΩ 0402; R_0402_1005Metric_Pad0.72x0.64mm_HandSolder
R_EN1, R_EN2, R_EN3: 10kΩ 0402; R_0402_1005Metric_Pad0.72x0.64mm_HandSolder
R_LEDpw1: 10kΩ 0402; R_0402_1005Metric_Pad0.72x0.64mm_HandSolder
R_M1S1, R_M1S2, R_M2S1, R_M2S2: 10kΩ 0402; R_0402_1005Metric_Pad0.72x0.64mm_HandSolder
R_PDN_UP1: 10kΩ 0402; R_0402_1005Metric_Pad0.72x0.64mm_HandSolder
R_TL1: 47Ω; R_0402_1005Metric_Pad0.72x0.64mm_HandSolder
R_UART1: 1kΩ 0402; R_0402_1005Metric_Pad0.72x0.64mm_HandSolder
R_cc1, R_cc2: 5.1kΩ; R_0402_1005Metric_Pad0.72x0.64mm_HandSolder
R_envRC1: 10kΩ 0402; R_0402_1005Metric_Pad0.72x0.64mm_HandSolder
R_gate1: 10kΩ 0402; R_0402_1005Metric_Pad0.72x0.64mm_HandSolder
R_in1: 100Ω 0402; R_0402_1005Metric_Pad0.72x0.64mm_HandSolder
R_statLED1: 330Ω; R_0402_1005Metric_Pad0.72x0.64mm_HandSolder
RbiasO1_1, RbiasO1_2, RbiasO2_1, RbiasO2_2, RbiasO2_3, RbiasO2_4: 10kΩ 0402; R_0402_1005Metric_Pad0.72x0.64mm_HandSolder
Rbleed1: 4.7kΩ; R_0402_1005Metric_Pad0.72x0.64mm_HandSolder
RfO1_1: 390Ω; R_Axial_DIN0207_L6.3mm_D2.5mm_P10.16mm_Horizontal
RfO2_A1, RfO2_B1: 910Ω; R_0402_1005Metric_Pad0.72x0.64mm_HandSolder
RgO1_1, RgO2_A1, RgO2_B1: 100Ω; R_0402_1005Metric_Pad0.72x0.64mm_HandSolder
Rsnub1: 10kΩ 0402; R_0402_1005Metric_Pad0.72x0.64mm_HandSolder
SK1_T1, SK1_T2, SK2_T1, SK2_T2: Conn_01x08; PinSocket_1x08_P2.54mm_Vertical
SK4, SK5: Conn_01x04; PinSocket_1x04_P2.54mm_Vertical
SW_boot1: 6×6mm tactile; SW_PUSH_6mm
SW_reset1: 6×6mm tactile; SW_PUSH_6mm
U1: ESP32-S3-WROOM-1
U2: LM2596S-5; TO-263-5_TabPin3
U3: AMS1117-3.3; SOT-223-3_TabPin2

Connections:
+3V3: CdecAD_C1.1, CdecAD_C8.2, CdecES_C1.2, CdecES_C8.2, CdecO1_C1.1, CdecO1_C8.1, CdecO2_C1.1, CdecO2_C8.1, CouLD_C1.1, CouLD_T1.1, Drx1.2 (A), Drx2.2 (A), IC1.8 (V+), IC2.8 (V+), J9.2, J15_1.1, J15_2.1, J16.1, J_AD9833.1, Jup_TMC1_extra1.1 (Pin_1_1), Jup_TMC1_extra2.1 (Pin_1_1), Jup_TMC2_extra1.1 (Pin_1_1), Jup_TMC2_extra2.1 (Pin_1_1), R_BOOT1.2, R_EN1.1, R_EN2.1, R_EN3.2, R_M1S1.1, R_M1S2.1, R_M2S1.1, R_M2S2.1, R_PDN_UP1.2, RbiasO1_1.1, RbiasO2_1.1, RbiasO2_3.1, SK2_T1.7, SK2_T2.7, SK4.4, SK5.4, U1.2 (3V3), U3.2 (VO)
+5V: CinLD_T1.1, CouBU_C1.1, CouBU_E1.1, Dusb1.1 (K), J8.1, J9.4, Lbuck1.1, Rbleed1.1, U2.4 (FB), U3.3 (VI)
+24V: C_inBU_C1.1, C_inBU_E1.1, CdecT1_C1.1, CdecT1_E1.1, CdecT2_C1.1, CdecT2_E1.1, Dclamp1.1 (K), F2.2, R_LEDpw1.1, SK2_T1.1, SK2_T2.1, U2.1 (VIN)
/AD9833_CS: J_AD9833.5, U1.31 (IO38)
/BTN1: J9.17, U1.19 (IO11)
/BUZ_PWM: J9.18, U1.21 (IO13)
/DIR_M1: SK1_T1.8, U1.6 (IO6)
/DIR_M2: SK1_T2.8, U1.17 (IO9)
/EC11_A: J9.13, U1.9 (IO16)
/EC11_B: J9.14, U1.10 (IO17)
/EC11_SW: J9.15, U1.11 (IO18)
/EN_M1: R_EN1.2, SK1_T1.1, U1.7 (IO7)
/EN_M2: R_EN2.2, SK1_T2.1, U1.18 (IO10)
/HX711_1_DT: SK4.2, U1.35 (IO42)
/HX711_2_DT: SK5.2, U1.23 (IO21)
/HX711_SCK: SK4.3, SK5.3, U1.30 (IO37)
/I2C_SCL: J15_1.4, J15_2.4, U1.37 (TXD0)
/I2C_SDA: J15_1.3, J15_2.3, U1.15 (IO3)
/LIMIT_M1: Clim1_C1.1, J6.2, U1.22 (IO14)
/LIMIT_M2: Clim2_C1.1, J7.2, U1.8 (IO15)
/M1_A1: J4.2, SK2_T1.4
/M1_A2: J4.1, SK2_T1.3
/M1_B1: J4.3, SK2_T1.5
/M1_B2: J4.4, SK2_T1.6
/M2_A1: J5.2, SK2_T2.4
/M2_A2: J5.1, SK2_T2.3
/M2_B1: J5.3, SK2_T2.5
/M2_B2: J5.4, SK2_T2.6
/RPi_RX: J3.2, U1.25 (IO48)
/RPi_TX: J3.3, U1.24 (IO47)
/RX_AMP_IN: CouAC_C1.1, Drx1.3 (K), R_in1.2
/SPI_CLK: J9.7, J_AD9833.4, U1.29 (IO36)
/SPI_MOSI: J9.5, J_AD9833.3, U1.28 (IO35)
/STAGE1_OUT: CouAC_C2.1, IC2.1 (OUTA), RfO2_A1.2
/STATUS_LED: R_statLED1.2, U1.38 (IO2)
/STEP_M1: SK1_T1.7, U1.5 (IO5)
/STEP_M2: SK1_T2.7, U1.12 (IO8)
/TFT_CS: J9.8, U1.32 (IO39)
/TFT_DC: J9.9, U1.33 (IO40)
/TFT_RST: J9.10, U1.34 (IO41)
/TMC1_extra1: J_extra_T1_fem1.1, J_extra_T1_mal1.1
/TMC1_extra2: J_extra_T1_fem1.2, J_extra_T1_mal1.2
/TMC2_extra1: J_extra_T2_fem1.1, J_extra_T2_mal1.1
/TMC2_extra2: J_extra_T2_fem1.2, J_extra_T2_mal1.2
/TMC_UART_RX: JMP_PDN_T1.2, JMP_PDN_T2.2, R_PDN_UP1.1, R_UART1.1, U1.36 (RXD0)
/TMC_UART_TX: R_UART1.2, U1.4 (IO4)
/TX_AMP_IN: CpreAC_C1.1, J_AD9833.7
/TX_OUT: CinAC_C1.2, J1.1 (In)
/T_CS: J9.11, U1.20 (IO12)
/T_DO: J9.6, U1.16 (IO46)
/T_IRQ: J9.12
/UAS_ADC: C_adc1.1, C_envRC1.1, Denv1.1 (K), Drx2.3 (K), R_envRC1.1, U1.39 (IO1)
/USB_D+: J13.A6 (D+), J13.B6 (D+), U1.14 (USB_D+)
/USB_D-: J13.A7 (D-), J13.B7 (D-), U1.13 (USB_D-)
GND: C_BOOT1.2, C_EN1.2, C_adc1.2, C_envRC1.2, C_inBU_C1.2, C_inBU_E1.2, CdecAD_C1.2, CdecAD_C8.1, CdecES_C1.1, CdecES_C8.1, CdecO1_C1.2, CdecO1_C8.2, CdecO2_C1.2, CdecO2_C8.2, CdecT1_C1.2, CdecT1_E1.2, CdecT2_C1.2, CdecT2_E1.2, CinLD_T1.2, Clim1_C1.2, Clim2_C1.2, CouBU_C1.2, CouBU_E1.2, CouLD_C1.2, CouLD_T1.2, Csnub1.2, Dcatch1.2 (A), Dclamp1.2 (A), Drx1.1 (K), Drx2.1 (K), IC1.4 (V-), IC2.4 (V-), J1.2 (Ext), J2.2 (Ext), J3.1, J6.1, J7.1, J8.2, J9.1, J9.3, J9.19, J13.A1 (GND), J13.A12 (GND), J13.B1 (GND), J13.B12 (GND), J13.SH (SHIELD), J14.2, J15_1.2, J15_2.2, J16.2, JMP_MS1_T1.1, JMP_MS1_T2.1, JMP_MS2_T1.1, JMP_MS2_T2.1, J_AD9833.2, J_AD9833.6, Jdo_TMC1_extra1.1 (Pin_1_1), Jdo_TMC1_extra2.1 (Pin_1_1), Jdo_TMC2_extra1.1 (Pin_1_1), Jdo_TMC2_extra2.1 (Pin_1_1), LED_pwr1.1 (K), LED_stat1.1 (K), R_cc1.2, R_cc2.2, R_envRC1.2, R_gate1.2, RbiasO1_2.2, RbiasO2_2.2, RbiasO2_4.2, Rbleed1.2, RgO1_1.1, RgO2_A1.1, RgO2_B1.2, SK1_T1.6, SK1_T2.6, SK2_T1.2, SK2_T1.8, SK2_T2.2, SK2_T2.8, SK4.1, SK5.1, SW_boot1.2, SW_reset1.2, U1.1 (GND), U1.40 (GND), U1.41 (GND), U2.3 (GND), U2.5 (~ON/OFF), U3.1 (GND)
unnamed: CinAC_C1.1, R_TL1.2
unnamed: Csnub1.1, Rsnub1.2
unnamed: Dcatch1.1 (K), Lbuck1.2, Rsnub1.1, U2.2 (OUT)
unnamed: Denv1.2 (A), IC2.7 (OUTB), RfO2_B1.2
unnamed: Dprot1.1 (A), Q1.4, R_gate1.1
unnamed: Dprot1.3 (K), J14.1, Q1.5, Q1.6, Q1.7, Q1.8
unnamed: Dusb1.2 (A), J13.A4 (VBUS), J13.A9 (VBUS), J13.B4 (VBUS), J13.B9 (VBUS)
unnamed: F2.1, Q1.1, Q1.2, Q1.3
unnamed: CpreAC_C1.2, IC1.3 (+INA), IC1.5 (+INB), RbiasO1_1.2, RbiasO1_2.1
unnamed: IC1.2 (-INA), RfO1_1.2, RgO1_1.2
unnamed: IC1.6 (-INB), IC1.7 (OUTB)
unnamed: IC1.1 (OUTA), R_TL1.1, RfO1_1.1
unnamed: CouAC_C1.2, IC2.3 (+INA), RbiasO2_1.2, RbiasO2_2.1
unnamed: CouAC_C2.2, IC2.5 (+INB), RbiasO2_3.2, RbiasO2_4.1
unnamed: IC2.2 (-INA), RfO2_A1.1, RgO2_A1.2
unnamed: IC2.6 (-INB), RfO2_B1.1, RgO2_B1.1
unnamed: J2.1 (In), R_in1.1
unnamed: J13.A5 (CC1), R_cc1.1
unnamed: J13.B5 (CC2), R_cc2.1
unnamed: JGPIO45.1 (Pin_1_1), U1.26 (IO45)
unnamed: JMP_MS1_T1.2, SK1_T1.2
unnamed: JMP_MS1_T1.3, R_M1S1.2
unnamed: JMP_MS1_T2.2, SK1_T2.2
unnamed: JMP_MS1_T2.3, R_M2S1.2
unnamed: JMP_MS2_T1.2, SK1_T1.3
unnamed: JMP_MS2_T1.3, R_M1S2.2
unnamed: JMP_MS2_T2.2, SK1_T2.3
unnamed: JMP_MS2_T2.3, R_M2S2.2
unnamed: JMP_PDN_T1.1, SK1_T1.5
unnamed: JMP_PDN_T1.3, SK1_T1.4
unnamed: JMP_PDN_T2.1, SK1_T2.5
unnamed: JMP_PDN_T2.3, SK1_T2.4
unnamed: LED_pwr1.2 (A), R_LEDpw1.2
unnamed: LED_stat1.2 (A), R_statLED1.1
unnamed: C_EN1.1, R_EN3.1, SW_reset1.1, U1.3 (EN)
unnamed: C_BOOT1.1, R_BOOT1.1, SW_boot1.1, U1.27 (IO0)

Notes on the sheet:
stage 1 set gain to 4.9
pre ADC processing
HF/LF power decoupling
AD9833 Signal Gen
HF/LF power decoupling
v2.5
RX Chain
note: only channel 1 is used channel 2 is kept stable by setting it as a unity gain follower
RX input protection
envelope rectifier diode
Version | Summary of change ----------------------------------------------------------------------- v2.0 | STM32G474 → ESP32-S3-WROOM-1-N8. USB-C native programming. BLE debug. v2.1 | UAS gain correction. TMC2209 VCP + SPREAD fixes. Power hardening. v2.2 | AO3401A → AO4407A + Zener. Motor 4×2-pin →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
EMBO MCU Board v3.4
envelope RC
AC coupling (blocks DC)
pre ADC filter (rec by espressif)
stage 1 set gain to 10.1
LDO 5V to 3V3
unity gain follower (tie off the unused channel)
catch diode
TL matching (reflected wave dampener)
EMBO MCU Board v3.4
UART to Rpi
snubber (damp HF)
1.65V bias
stage 2 set gain to 10.1
to motor coils
01/07/2026
24V to 5V Buck Converter
Boot Circuit
USB-C
RX amplifier
MCU
Load Cell Amplifiers
TX Chain
TX amplifier
12C Backup Sensor Connectors
clamps voltage transients above 28V
switching inductor
power decoupling
Inverse and reverse polarity protection
